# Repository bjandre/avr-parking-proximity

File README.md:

Code and electrical schematic for a garage parking proximity meter.

# Hardware:
* MCU - Atmel AVR attiny2313
* Ultrasonic distance sensor - MaxBotix LV-MaxSonar-EZ
* Adafruit LIPO/Li-Ion battery charging circut

# source
* 3rd-party/ - 3rd-party dependancies

* utils/ - break out reusable code for bit operations and led manipulation, with unit tests

* sonar-pwm-3led/ - receive sonar signal via a pulse width signal, change LED color depending on distance.

* sonar-usart-3led-sleep/ - receive sonar signal over serial signal, change LED color depending on distance, sleep mcu when readings are stable, periodically wake to detect changes.

# External dependencies

Build and flash requires avr-gcc, avr-libc and avrdude

Building on macOS with homebrew requires:

* avrdude
* osx-cross/avr/avr-gcc
* osx-cross/avr/avr-libc
* osx-cross/avr/avr-binutils

cmocka is used for C unit testing. Source is included in this repo,
and can be built with:

    cd 3rd-party
    make cmocka
    
Circuit schematic requires [KiCad](http://kicad-pcb.org/)

# TODO
* disable sonar ranging and periodically wake up to preserve battery.

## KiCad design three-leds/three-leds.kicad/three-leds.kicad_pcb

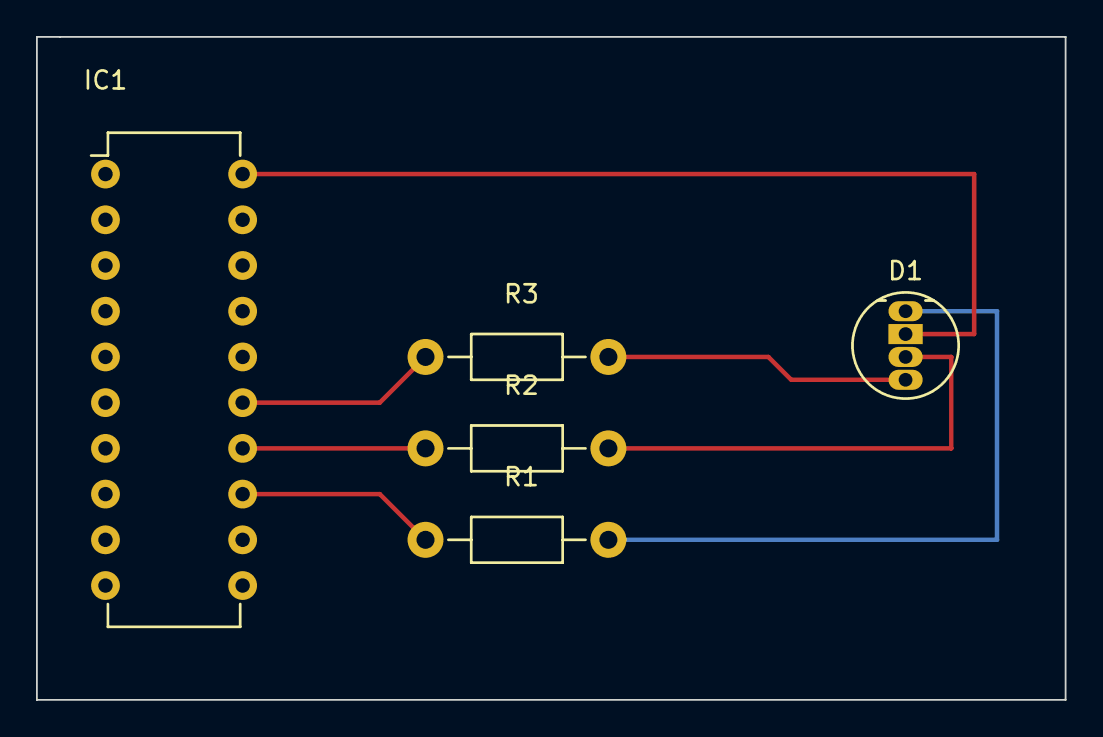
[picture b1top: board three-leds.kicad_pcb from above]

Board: 2 copper layers, 57.2 x 36.8 mm, 5 parts (0 on the bottom side), 7 nets.

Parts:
D1: LED_RABG; LED-RGB-5MM_Common_Cathode
IC1: ATTINY2313-P; DIP-20_W7.62mm
R1, R2, R3: R; Resistor_Horizontal_RM10mm

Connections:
unnamed: D1.1, R1.2
unnamed: D1.3, R2.2
unnamed: D1.4, R3.2
unnamed: IC1.13, R1.1
unnamed: IC1.14, R2.1
unnamed: IC1.15, R3.1
VCC: D1.2, IC1.20

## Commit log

2015-10-11 First working version of blinking a single LED on the attiny2313. Makefile to compile with avr-gcc and load code to chip with avrdude.
2015-10-11 Add program to turn on three LEDs sequentially
    Add a program to turn on three LEDs sequentially, overflowing the delay_ms
    timer to get a longer, low resolution timer. Update readme notes with low
    resolution timer info.
2015-10-11 Cleanup markdown formatting, add some notes.
2015-10-11 Fix markdown formatting in README
2015-10-31 Updated notes and working code for driving a single led with pwm on the attiny2313.
2015-10-31 Update notes about LED in source, add kicad schematic for layout. note LED pin order is RABG.
2015-11-13 example code and schematic to blink a RGB led with PWM on the attiny2313.
2016-01-29 cmocka tpl, utilities with unit tests, start sonar
    Start work on sonar program. Configure USART for the MaxBotix
    LV-MaxSonar-EZ MB1010. Need to work on interupts and receiving the sonar
    range value.
    Add cmocka as a third party library. Break out some utility functions
    for common bit operations and wrappers for turning the led on and off
    and changing the color. Unit test utility functions.
2016-01-31 Bug fix in make rules compiling and linking
    Need to add '-c' to compiling and cflags to linking to generate proper
    executable code when linking multiple files.
2016-01-31 Convert bit operations to using unit tested functions.
    Convert more bit wise operations to using unit tested functions from
    bit-ops library.
    Tested on board.
2016-01-31 Code cleanup
    Cleanup some comments, move main function, push code to cycle led into
    its own function.
    Tested on board - ok.
2016-01-31 Create USART received interrupt
    Enable global interrupts and create the interrupt service routine for
    USART RX complete.
    Testing on board - ok
2016-02-01 convert sonar data to integer range
    Initialize a string buffer for storing the sonar characters received
    over USART. Store the characters as they are received. Convert to an
    integer when a full string has been received. Unit tests for sonar
    string functions.
    Unit tests - pass
    Tested on board - led init ok, appears that USART interrupt is not firing?
2016-02-01 utility function to set led to white.
    Unit tests - pass
    Test on board - same as previous commit.
2016-02-02 Update interface to convert sonar string to int.
    Update the interface for converting the sonar string to an integer, now
    return the range instead of modifying in place. New unit test, modify
    tests in a really horrible way to do multiple assertions inside each
    test.
    Unit tests - pass
    Test on board - ok, USART interrupt still not being triggered.
2016-02-12 Create utility library for reusable code
    Move bit operations and rgb led operations into a separate directory and
    library.
    Unit tests: pass
    On board: rgb led works as expected. usart between sonar and attiny still
    doesn't work.
2016-02-14 Working proximity sensor with sonar pulse width
    Working proximity sensor measuring sonar pulse with with the input capture pin
    and interrupts.
    Unit tests: pass
    On board tesing: works with color change from 30 - 60 inches.
2016-02-15 Rename readme to dev-notes, new readme file.
    Testing: none, no code changes.
2016-02-15 Update kicad schematics for sonar projects.
    Add the transistor for rs232 to ttl logic levels to the sonar-usart schematic.
    Create schematic for the sonar-pwm project.
    Testing: none, no changes to code.
2016-04-16 Original implementation of bit ops library was subject to race conditions because of copying, modifying, and reassigning buffers. Race conditions were unlikely in the sonar use case. Convert bit ops 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
    Tests - pass
2016-06-30 Make space in the sonar usart string for the null character.
    Tests: pass
2016-06-30 Bug fix for usart receiver from sonar
    Don't use asynchronous mode for the receiver. For some reason it never
    triggers the interrupt or stores the received bit.
    Add debugging logic to echo the received character back out on the usart
    TX line.
    Tests: pass
2016-07-06 Update kicad files for the sonar-usart-3led schematic. not complete, external oscillator needs to be updated. pin conflict on tiny and sonar ground?
2016-07-07 Copy the sonar-usart project into a new directory to introduce sleep mode.
2016-07-16 Initial power management for proximity meter
    Setup sleep mode, powering down the led and signal the sonar to stop
    ranging when the range isn't changing. Need to do better delta range
    management. Setup a watchdog timer to trigger an interrupt and wake from
    sleep.
    Testing: unit tests pass. Manual testing of range-led behavior correct.
2016-07-16 Cleanup int type of range.
    Numerical value of range sent by sonar is 0-254 inches. Store in a uint8
    instead of uint16 so we can do all range operations in a single machine
    instruction on the 8 bit processor. Add -Wall to compiler flags for
    sonar string tests.
    Testing: unit tests pass. Manual range-led testing passed.
2016-07-16 async cleanup
    Move global data that is accessed asynchronously by the main loop and
    interrupts into a struct. Limit access to the struct so it is easier to
    ensure that it happens in regions with interrupts disabled. Cleanup of
    local range data.
    Testing: unit tests pass. Manual range-led testing passed.
2016-07-20 Change approach to turning off led during sleep
    Setting the output pin to zero logic level doesn't necessarily set the voltage
    to ground. The remaining current flowing through the pin is enough to light the
    led. As a result the original method of turning off the led by setting the
    anode pin to zero doesn't work unless a transistor is attached to the pin to
    sink the line to ground. For now, add a new led_off method that sets the anode
    to zero and all the cathodes to one. Then the resulting current can't flow
2016-07-21 Add timer to to monitor changes in range
    Setup the 16 bit timer / counter 1 and an additional software counter as
    a way to monitor the changes in range. Every time the delta_range
    exceeds a cutoff, we reset the timers. When the hardware counter
    overflows, it triggers an interrupt that increments the software
    counter. If the range is in a steady state, we go to sleep.
    Testing: unit tests pass, manual sonar testing ok.
2016-09-18 Bug fix setting bits for sleep counter.
    Testing: compiles and runs, sensor controls led.
2016-09-20 Bugfix: initialize range timer
    Need to turn on the timer 1 overflow interrupt. It also helps to
    actually call the initialization of the range timer.
    Testing: manually verified that the interrupt is called with a temporary
    abort statement. Sonar and led work with manual testing.
2016-09-20 Decrease timer 1 pre-scaling and steady state range limit so we get about 30 seconds of checking before going to sleep.
    Testing: manually run with abort statement to see when sleep was
    triggered.
2016-09-20 Use the 'true' led off function so there is no voltage leak keeping the led lit when it should be off. Move led color selection into an else block so it is only done if the sonar range is not at stea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
    Testing: unit tests - pass
    manual testing of sonar/led range, including going to sleep
    with led off and waking up.
2016-09-21 Bugfix: need to pull the ranging pin high for a minimum of 20 microseconds to trigger ranging. If the delay is missing, the sonar seems to report the minimum distance.... Possible that the main event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
    Testing: manually tested sleep, ranging and led.
2016-09-23 Bugfix: allow sonar a complete ranging cycle upon wakeup
    The event loop is very short, and it's likely that we are
    trying to turn the sonar on/off in the middle of a ranging cycle...?
    Setting a delay to ensure one complete cycle ensures we get a new data
    point and seems to prevent a bug where the sonar gets stuck at the
    minimum range.
    Testing: manually tested sonar, led, sleep.
2016-09-23 Cleanup constants.
    Replace a couple of magic numbers with constants, convert some macros to
    static constants.
    Testing: compiles, manually run sonar, led, sleep work.
2016-09-23 Cleanup initialization of range state.
    Testing: compiles, runs with manual testing of sonar, led, sleep.
2016-09-25 Move hardware initialization into a function. Add a few comments to clarify call ordering.
    Testing: manual testing of led, sonar and sleep.
2016-10-17 Async data should be defined as volatile.
    Testing: clean compile and build. Manual testing of ranging and sleep.
2016-11-11 Remove code to turn sonar ranging on and off.
    Hardware to turn ranging on and off isn’t in place. Remove the code
    that is intended to turn ranging on and off. Update some comments.
    Testing: unit tests - pass
    manually test ranging, sleep.
2016-11-11 Bug fix in makefile, remove utils library during clean.
    Testing: make clean, no software/hardware testing.
2016-11-12 Remove some of the old software versions for intermediate versions of the hardware.
    Testing: none
2016-12-04 Cleanup README
